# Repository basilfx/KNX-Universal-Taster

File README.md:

# KNX Universal Taster
DIY universal taster interface for the KNX bus.

## Introduction
This repository contains my designs for creating a custom KNX universal taster
interface (or actor). This is board that can be used for several purposes, but
its main purpose is to convert pulse-based wall switches into KNX-enabled
switches. The boards are designed to be small and should fit wall boxes with a
depth of 50 mm.

I currently have 25 boards installed in my house. As of writing (January 2021),
they have been running for more than two years.

## Features
While commercial alternatives exists, for example the [MDT Universal Interface](https://www.mdt.de/EN_Universal_Interface.html)
or the [ABB Universal Interface](https://new.abb.com/products/GHQ6310070R0111/us-u4-2-universal-interface-4-fold-fm),
I challenged myself to create a version that has more capabilities:

* Smaller.
* Programmable button options, e.g. multiple presses, long(er) presses.
* Support for (environmental) sensors.
* Universal use: data loggers, protocol gateways (Modbus, DSMR).
* Remote configuration via ETS or other software.

## Contents
You can find the following in this repository:

* [3D prints](3d) - Printable parts, such as an enclosure
* [Firmware](firmware) - Firmware files
* [PCB designs](pcb) - KiCad designs for the main PCB and extensions

## Support
You can buy the boards from [Aisler.net](https://aisler.net/p/GGKCSYBF), and
help me to support the development.

## License
The work in this repository is covered by CC BY-NC-SA 4.0. See the `LICENSE.md`
file for more information.

## Disclaimer
Use this project or information at your own risk. I cannot be held responsible
for any injuries or damages.

This page and its content is not affiliated with the KNX Association. Most
certainly, this work is not certified by the KNX Association.

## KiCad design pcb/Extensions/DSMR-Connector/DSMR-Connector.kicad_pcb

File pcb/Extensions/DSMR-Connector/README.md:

# DSMR-Connector

## Introduction
This board converts the P1 port found on Dutch Smart Energy Meters to UART,
opto-isolated from the Taster module. You can find more information in the
[P1 Companion Standard](https://www.netbeheernederland.nl/_upload/Files/Slimme_meter_15_a727fce1f1.pdf).

This board is only compatible with DSMR 5.0, since that version is using two
additional pins (therefore RJ-12 instead of RJ-11) to supply the bidirectional
optocoupler.

## Board

## Schema
You can find the schema [here](DSMR-Connector.pdf).

## BoM
The (interactive) BoM can be found [here](https://basilfx.github.io/KNX-Universal-Taster/pcb/Extensions/DSMR-Connector/BoM/ibom.html).

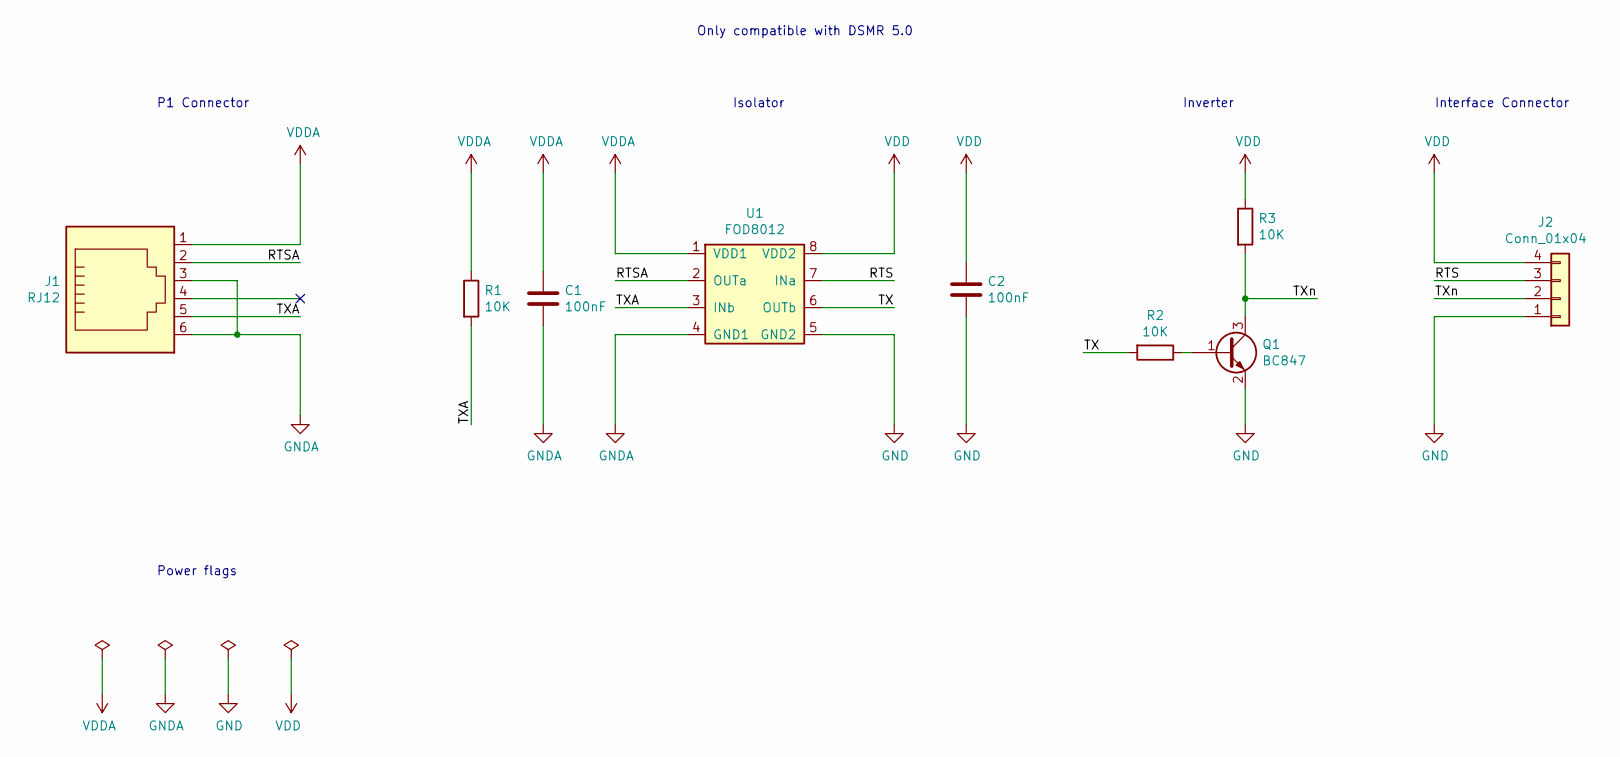
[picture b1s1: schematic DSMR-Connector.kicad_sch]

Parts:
C1, C2: 100nF; C_0603_1608Metric
J1: RJ12; RJ12_Amphenol_54601
J2: Conn_01x04; PinHeader_1x04_P1.27mm_Vertical
Q1: BC847; SOT-23
R1, R2, R3: 10K; R_0603_1608Metric
U1: FOD8012; SOIC-8-N

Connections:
/RTS: J2.3, U1.7 (INa)
/RTSA: J1.2, U1.2 (OUTa)
/TX: R2.2, U1.6 (OUTb)
/TXA: J1.5, R1.2, U1.3 (INb)
/TXn: J2.2, Q1.3 (C), R3.2
GND: C2.2, J2.1, Q1.2 (E), U1.5 (GND2)
GNDA: C1.2, J1.3, J1.6, U1.4 (GND1)
unnamed: Q1.1 (B), R2.1
VDD: C2.1, J2.4, R3.1, U1.8 (VDD2)
VDDA: C1.1, J1.1, R1.1, U1.1 (VDD1)

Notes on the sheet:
Inverter
Isolator
Power flags
P1 Connector
Only compatible with DSMR 5.0
Interface Connector

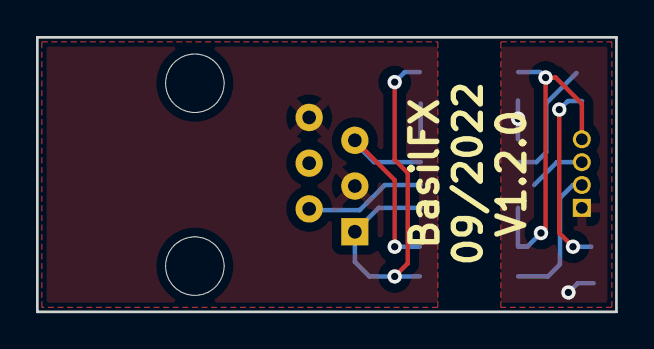
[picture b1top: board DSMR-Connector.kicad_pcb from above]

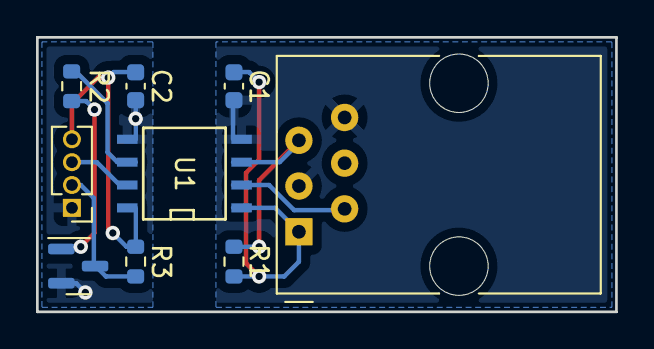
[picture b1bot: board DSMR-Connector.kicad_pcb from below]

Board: 2 copper layers, 32.2 x 15.2 mm, 9 parts (9 on the bottom side), 10 nets.

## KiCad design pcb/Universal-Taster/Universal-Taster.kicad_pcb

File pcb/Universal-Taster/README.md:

# Universal Taster

## Features
* ARM Cortex M4 CPU with 1 MiB of flash and 256 KiB of RAM
* Compatible with OnSemi NCN5120 and NCN5121
* 8 Mbit SPI NOR flash
* 6 universal GPIO pins
* 2 pins for I2C
* 2 RX/TX pins (without header)
* 30x30x15 mm footprint (including connector)

## Pictures

## Board

## Schema
You can find the schema [here](Universal-Taster.pdf).

## Compatibility
This board is compatible with the [OnSemi NCN5121](http://www.onsemi.com/pub/Collateral/NCN5121-D.PDF)
or the [OnSemi NCN5120](http://www.onsemi.com/pub/Collateral/NCN5120-D.PDF).

## BoM
The (interactive) BoM can be found [here](https://basilfx.github.io/KNX-Universal-Taster/pcb/Universal-Taster/BoM/ibom.html).

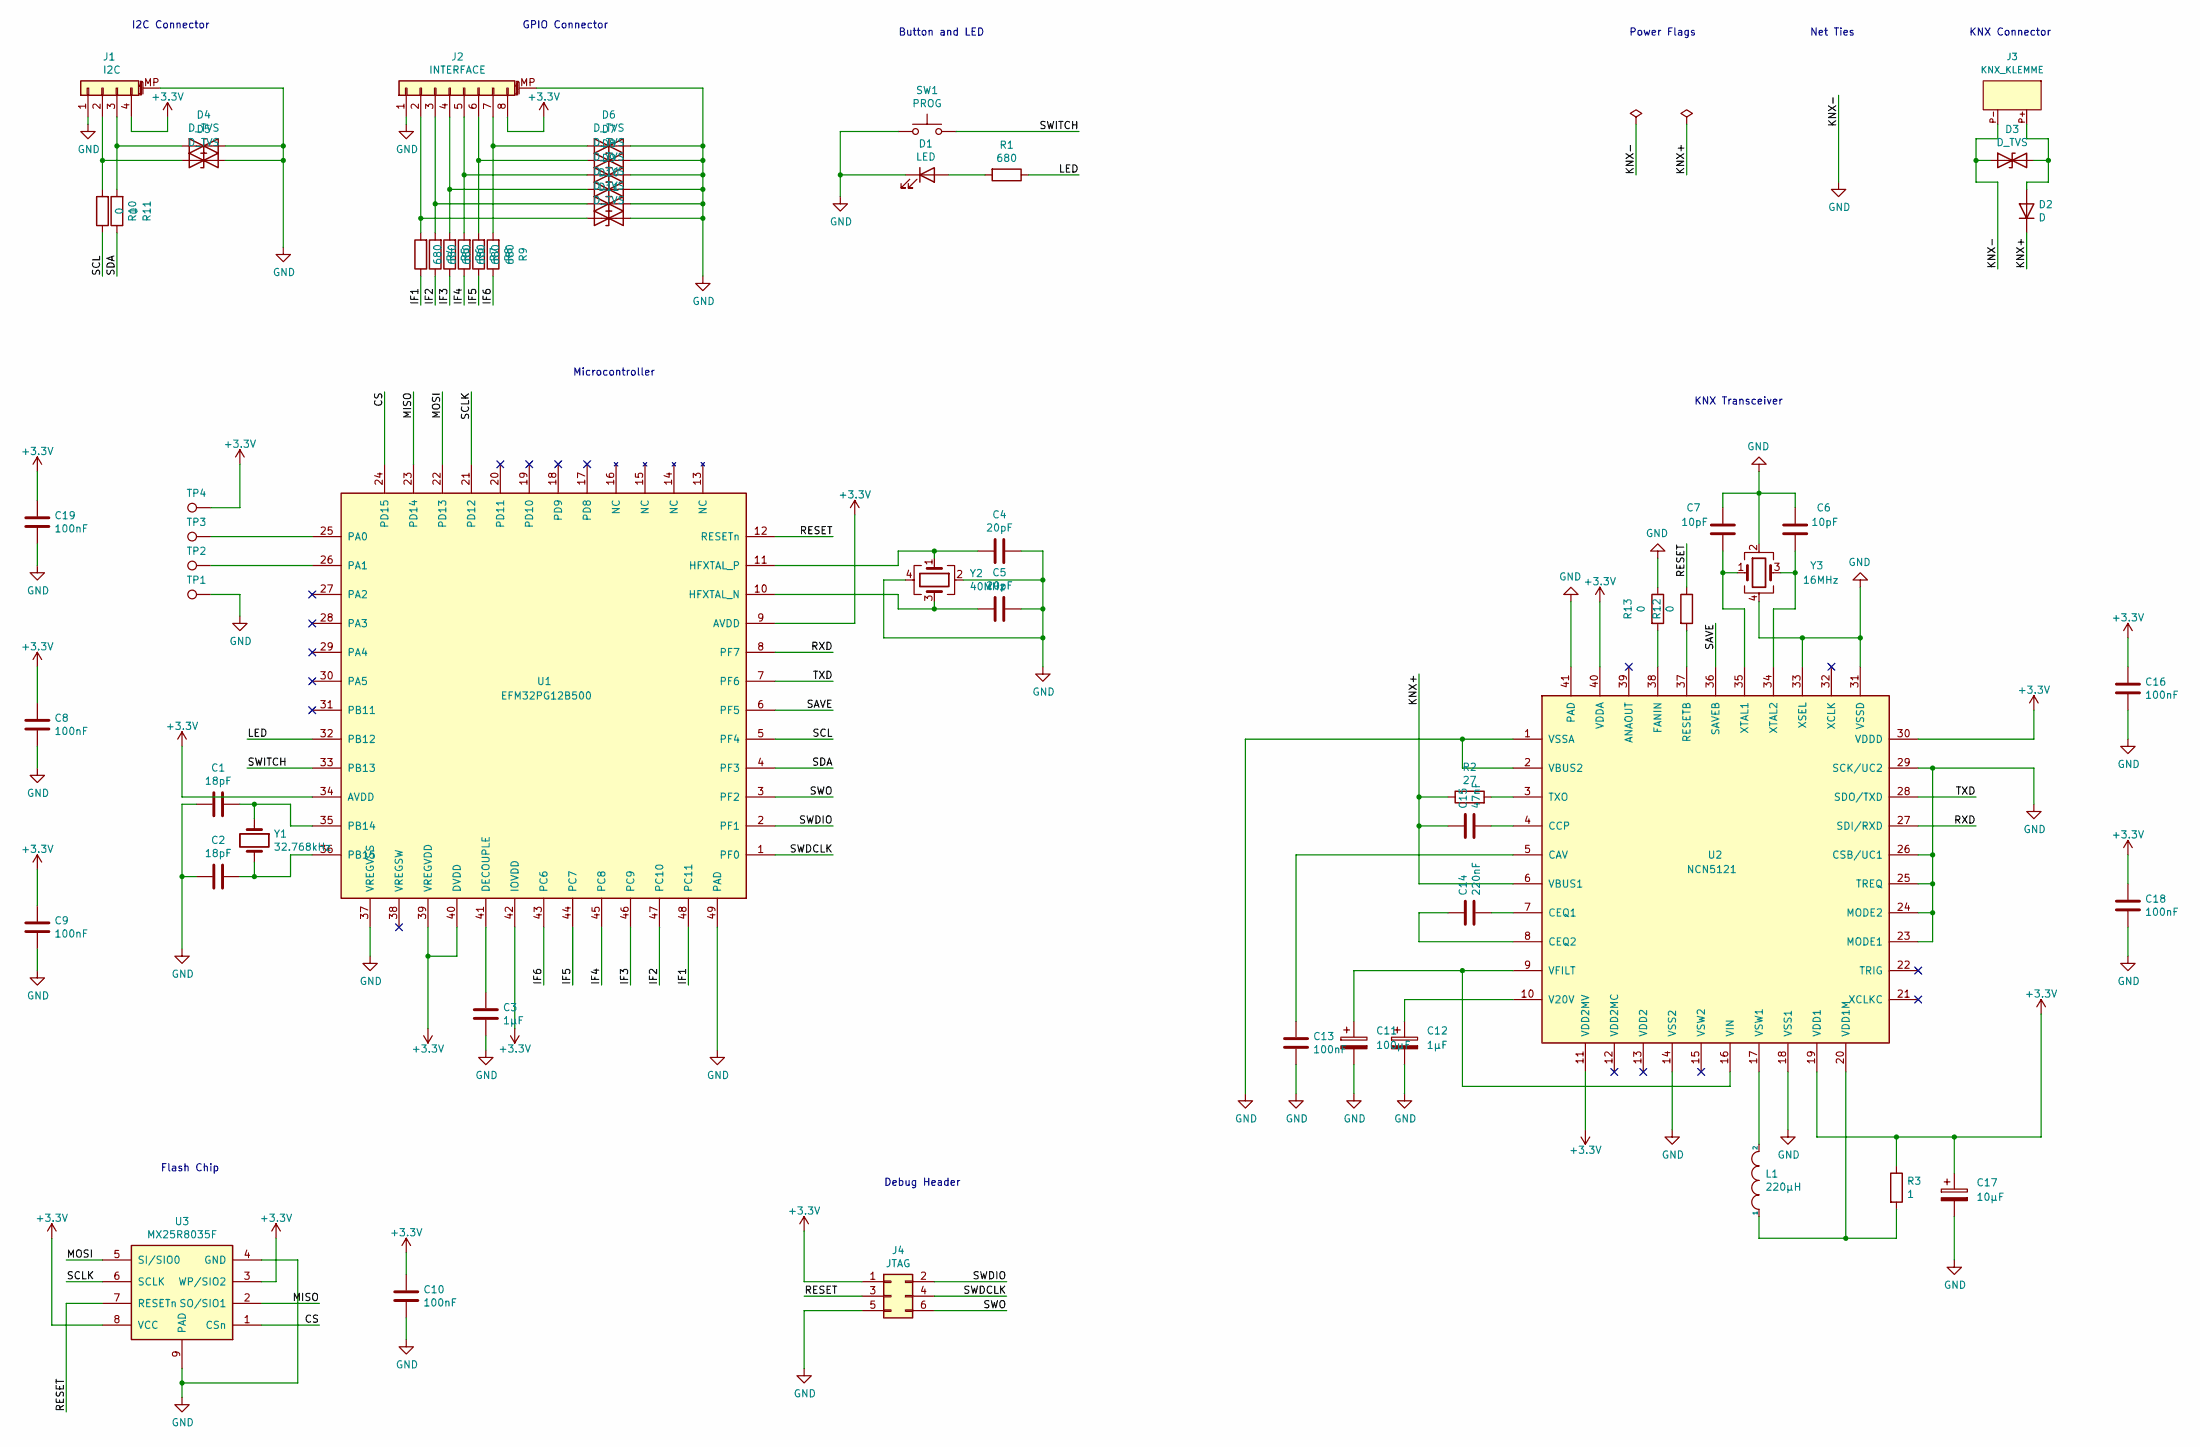
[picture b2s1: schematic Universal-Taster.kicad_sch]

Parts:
C1, C2: 18pF; C_0603_1608Metric
C3: 1µF; C_0603_1608Metric
C4, C5: 20pF; C_0603_1608Metric
C6, C7: 10pF; C_0603_1608Metric
C8, C9, C10, C13, C16, C18, C19: 100nF; C_0603_1608Metric
C11: 100µF; CP_Elec_6.3x7.7
C12: 1µF; C_0805_2012Metric
C14: 220nF; C_0603_1608Metric
C15: 47nF; C_0603_1608Metric
C17: 10µF; C_0603_1608Metric
D1: LED; LED_0603_1608Metric
D2: D; D_SMB
D3: D_TVS; D_SMB
D4, D5, D6, D7, D8, D9, D10, D11: D_TVS; D_0603_1608Metric
J1: I2C; JST_SH_BM04B-SRSS-TB_1x04-1MP_P1.00mm_Vertical
J2: INTERFACE; JST_SH_BM08B-SRSS-TB_1x08-1MP_P1.00mm_Vertical
J3: KNX_KLEMME
J4: JTAG; PinHeader_2x03_P1.27mm_Vertical_SMD
L1: 220µH; L_Bourns-SRR5028
R1, R4, R5, R6, R7, R8, R9: 680; R_0603_1608Metric
R2: 27; R_2512_6332Metric
R3: 1; R_0603_1608Metric
R10, R11, R12, R13: 0; R_0603_1608Metric
SW1: PROG; SW_SPST_B3U-1000P
TP1, TP2, TP3, TP4: Test_Point; TestPoint_Pad_D1.0mm
U1: EFM32PG12B500; Infineon_MLPQ-48-1EP_7x7mm_P0.5mm_Pad5.15x5.15mm
U2: NCN5121; QFN-40-1EP_6x6mm_P0.5mm_EP4.6x4.6mm
U3: MX25R8035F; USON-8_2x3mm_P0.5mm
Y1: 32.768kHz; Crystal_SMD_2012-2Pin_2.0x1.2mm
Y2: 40MHz; Crystal_SMD_2016-4Pin_2.0x1.6mm
Y3: 16MHz; Crystal_SMD_2016-4Pin_2.0x1.6mm

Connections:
+3.3V: C8.1, C9.1, C10.1, C16.1, C17.1, C18.1, C19.1, J1.4, J2.8, J4.1, R3.1, TP4.1, U1.9 (AVDD), U1.34 (AVDD), U1.39 (VREGVDD), U1.40 (DVDD), U1.42 (IOVDD), U2.11 (VDD2MV), U2.19 (VDD1), U2.30 (VDDD), U2.40 (VDDA), U3.3 (WP/SIO2), U3.8 (VCC)
/CS: U1.24 (PD15), U3.1 (CSn)
/IF1: R4.1, U1.48 (PC11)
/IF2: R5.1, U1.47 (PC10)
/IF3: R6.1, U1.46 (PC9)
/IF4: R7.1, U1.45 (PC8)
/IF5: R8.1, U1.44 (PC7)
/IF6: R9.1, U1.43 (PC6)
/KNX+: C15.1, D2.1 (K), R2.1, U2.6 (VBUS1)
/LED: R1.1, U1.32 (PB12)
/MISO: U1.23 (PD14), U3.2 (SO/SIO1)
/MOSI: U1.22 (PD13), U3.5 (SI/SIO0)
/RESET: J4.3, R12.1, U1.12 (RESETn), U3.7 (RESETn)
/RXD: U1.8 (PF7), U2.27 (SDI/RXD)
/SAVE: U1.6 (PF5), U2.36 (SAVEB)
/SCL: R10.1, U1.5 (PF4)
/SCLK: U1.21 (PD12), U3.6 (SCLK)
/SDA: R11.1, U1.4 (PF3)
/SWDCLK: J4.4, U1.1 (PF0)
/SWDIO: J4.2, U1.2 (PF1)
/SWITCH: SW1.2, U1.33 (PB13)
/SWO: J4.6, U1.3 (PF2)
/TXD: U1.7 (PF6), U2.28 (SDO/TXD)
GND: C1.1, C2.1, C3.2, C4.2, C5.2, C6.2, C7.2, C8.2, C9.2, C10.2, C11.2, C12.2, C13.2, C16.2, C17.2, C18.2, C19.2, D1.1 (K), D3.1 (A1), D4.2 (A2), D5.2 (A2), D6.2 (A2), D7.2 (A2), D8.2 (A2), D9.2 (A2), D10.2 (A2), D11.2 (A2), J1.1, J1.MP (MountPin), J2.1, J2.MP (MountPin), J3.P- (-), J4.5, R13.1, SW1.1, TP1.1, U1.37 (VREGVSS), U1.49 (PAD), U2.1 (VSSA), U2.2 (VBUS2), U2.14 (VSS2), U2.18 (VSS1), U2.23 (MODE1), U2.24 (MODE2), U2.25 (TREQ), U2.26 (CSB/UC1), U2.29 (SCK/UC2), U2.31 (VSSD), U2.33 (XSEL), U2.41 (PAD), U3.4 (GND), U3.9 (PAD), Y2.2, Y2.4, Y3.2, Y3.4
unnamed: C1.2, U1.35 (PB14), Y1.1
unnamed: C2.2, U1.36 (PB15), Y1.2
unnamed: C3.1, U1.41 (DECOUPLE)
unnamed: C4.1, U1.11 (HFXTAL_P), Y2.1
unnamed: C5.1, U1.10 (HFXTAL_N), Y2.3
unnamed: C6.1, U2.34 (XTAL2), Y3.3
unnamed: C7.1, U2.35 (XTAL1), Y3.1
unnamed: C11.1, U2.9 (VFILT), U2.16 (VIN)
unnamed: C12.1, U2.10 (V20V)
unnamed: C13.1, U2.5 (CAV)
unnamed: C14.1, U2.8 (CEQ2)
unnamed: C14.2, U2.7 (CEQ1)
unnamed: C15.2, U2.4 (CCP)
unnamed: D1.2 (A), R1.2
unnamed: D2.2 (A), D3.2 (A2), J3.P+ (+)
unnamed: D4.1 (A1), J1.3, R11.2
unnamed: D5.1 (A1), J1.2, R10.2
unnamed: D6.1 (A1), J2.7, R9.2
unnamed: D7.1 (A1), J2.6, R8.2
unnamed: D8.1 (A1), J2.5, R7.2
unnamed: D9.1 (A1), J2.4, R6.2
unnamed: D10.1 (A1), J2.3, R5.2
unnamed: D11.1 (A1), J2.2, R4.2
unnamed: L1.1, R3.2, U2.20 (VDD1M)
unnamed: L1.2, U2.17 (VSW1)
unnamed: R2.2, U2.3 (TXO)
unnamed: R12.2, U2.37 (RESETB)
unnamed: R13.2, U2.38 (FANIN)
unnamed: TP2.1, U1.26 (PA1)
unnamed: TP3.1, U1.25 (PA0)

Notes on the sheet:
Power Flags
KNX Transceiver
I2C Connector
Debug Header
Net Ties
GPIO Connector
Microcontroller
Button and LED
KNX Connector
Flash Chip

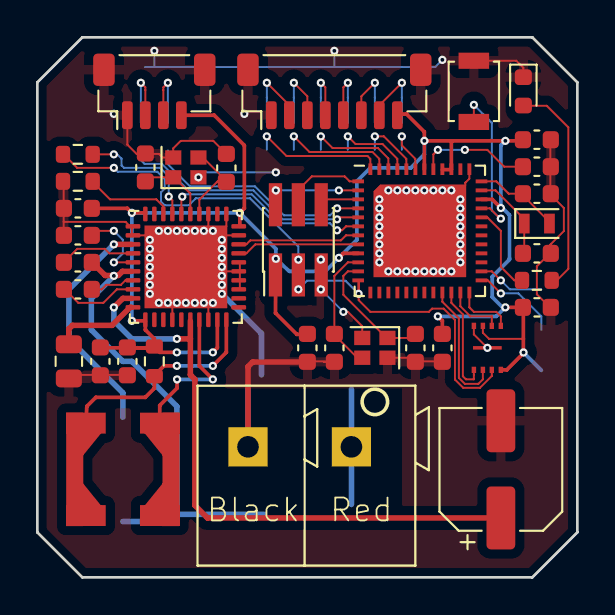
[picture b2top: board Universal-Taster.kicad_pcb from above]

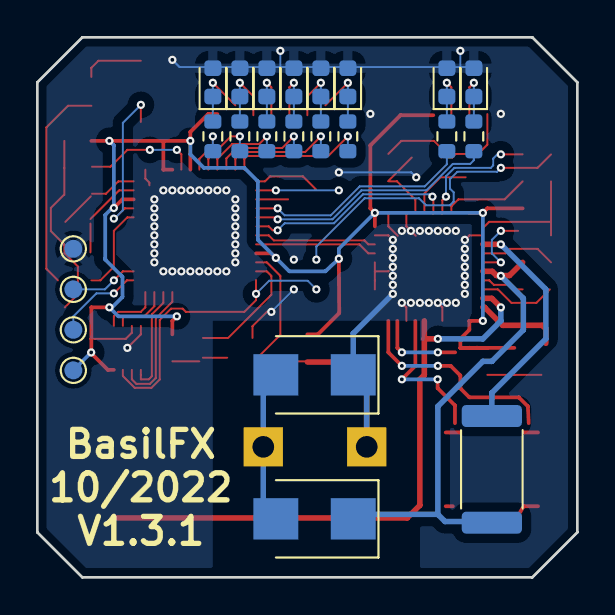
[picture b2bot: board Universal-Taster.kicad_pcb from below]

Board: 2 copper layers, 30.0 x 30.0 mm, 59 parts (23 on the bottom side), 54 nets.

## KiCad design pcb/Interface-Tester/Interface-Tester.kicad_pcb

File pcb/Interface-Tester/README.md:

# Interface Tester

## Introduction
This is an interface tester for the taster board. It is used for verification
purposes

## Board

## Schema
You can find the schema [here](Interface-Tester.pdf).

## BoM
The (interactive) BoM can be found [here](https://basilfx.github.io/KNX-Universal-Taster/pcb/Interface-Tester/BoM/ibom.html).

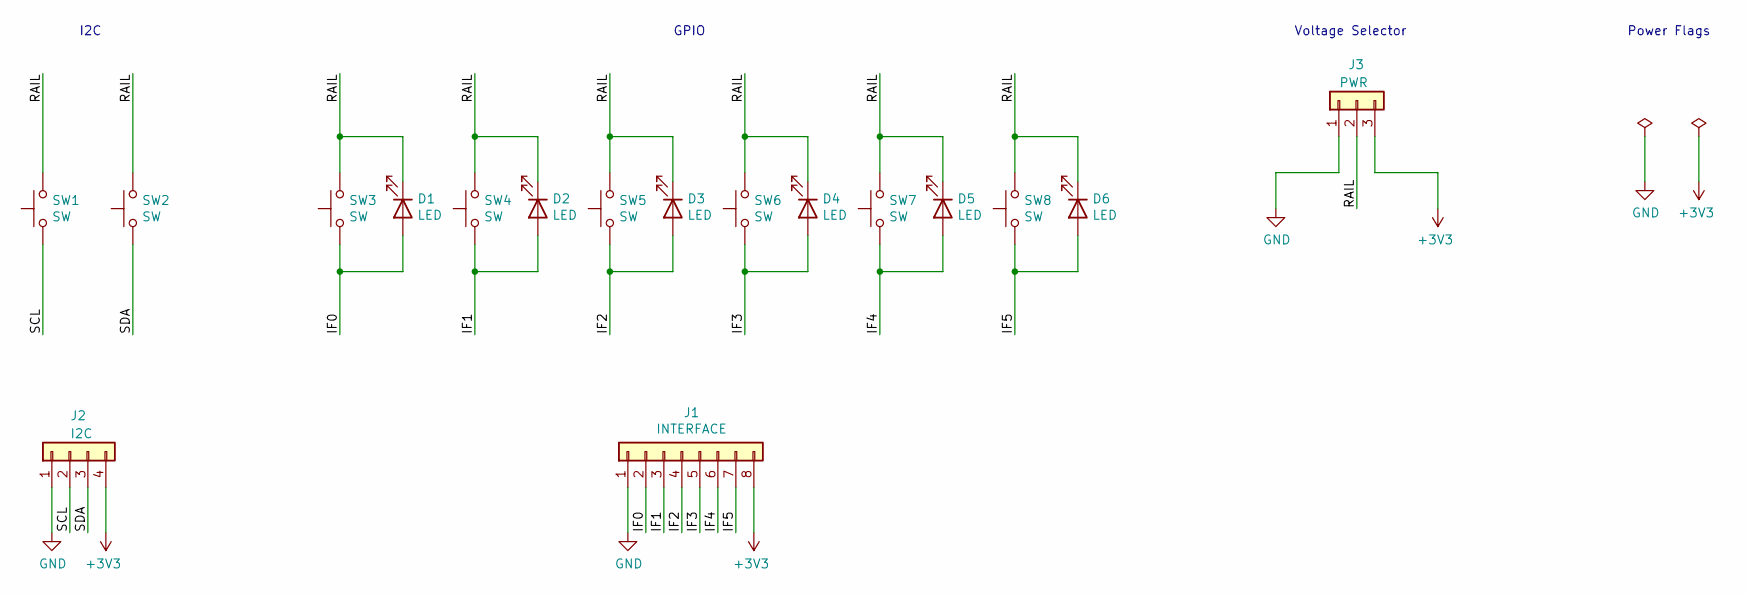
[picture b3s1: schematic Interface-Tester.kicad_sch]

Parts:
D1, D2, D3, D4, D5, D6: LED; LED_0603_1608Metric
J1: INTERFACE; PinHeader_1x08_P2.54mm_Vertical
J2: I2C; PinHeader_1x04_P2.54mm_Vertical
J3: PWR; PinHeader_1x03_P2.54mm_Vertical
SW1, SW2, SW3, SW4, SW5, SW6, SW7, SW8: SW; SW_PUSH_6mm

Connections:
+3V3: J1.8, J2.4, J3.3
/IF0: D1.2 (A), J1.2, SW3.1
/IF1: D2.2 (A), J1.3, SW4.1
/IF2: D3.2 (A), J1.4, SW5.1
/IF3: D4.2 (A), J1.5, SW6.1
/IF4: D5.2 (A), J1.6, SW7.1
/IF5: D6.2 (A), J1.7, SW8.1
/RAIL: D1.1 (K), D2.1 (K), D3.1 (K), D4.1 (K), D5.1 (K), D6.1 (K), J3.2, SW1.2, SW2.2, SW3.2, SW4.2, SW5.2, SW6.2, SW7.2, SW8.2
/SCL: J2.2, SW1.1
/SDA: J2.3, SW2.1
GND: J1.1, J2.1, J3.1

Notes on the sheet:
Voltage Selector
GPIO
Power Flags
I2C

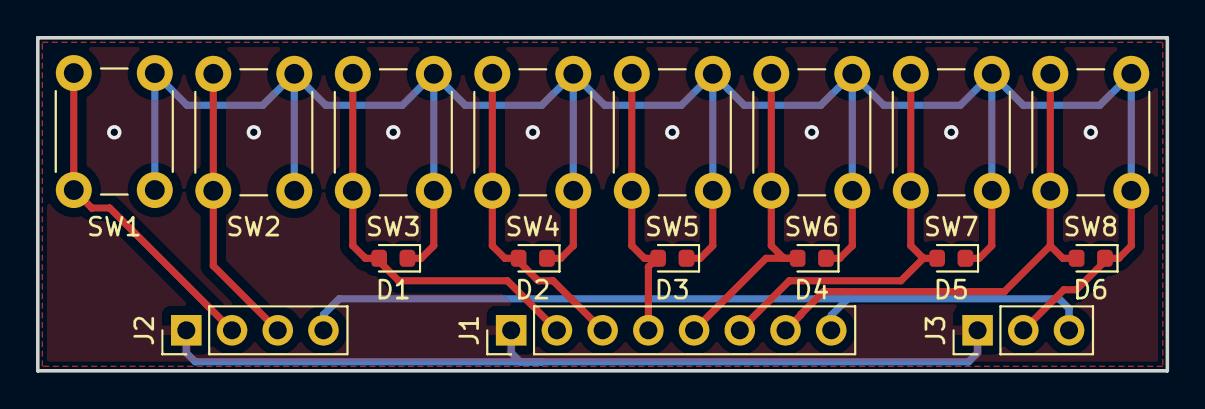
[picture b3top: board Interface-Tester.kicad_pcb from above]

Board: 2 copper layers, 62.8 x 18.5 mm, 17 parts (0 on the bottom side), 11 nets.

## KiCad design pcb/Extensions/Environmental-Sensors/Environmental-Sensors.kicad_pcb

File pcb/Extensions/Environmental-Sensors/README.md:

# Environmental-Sensors

## Board

## Schema
You can find the schema [here](Environmental-Sensors.pdf).

## BoM
The (interactive) BoM can be found [here](https://basilfx.github.io/KNX-Universal-Taster/pcb/Extensions/Environmental-Sensors/BoM/ibom.html).

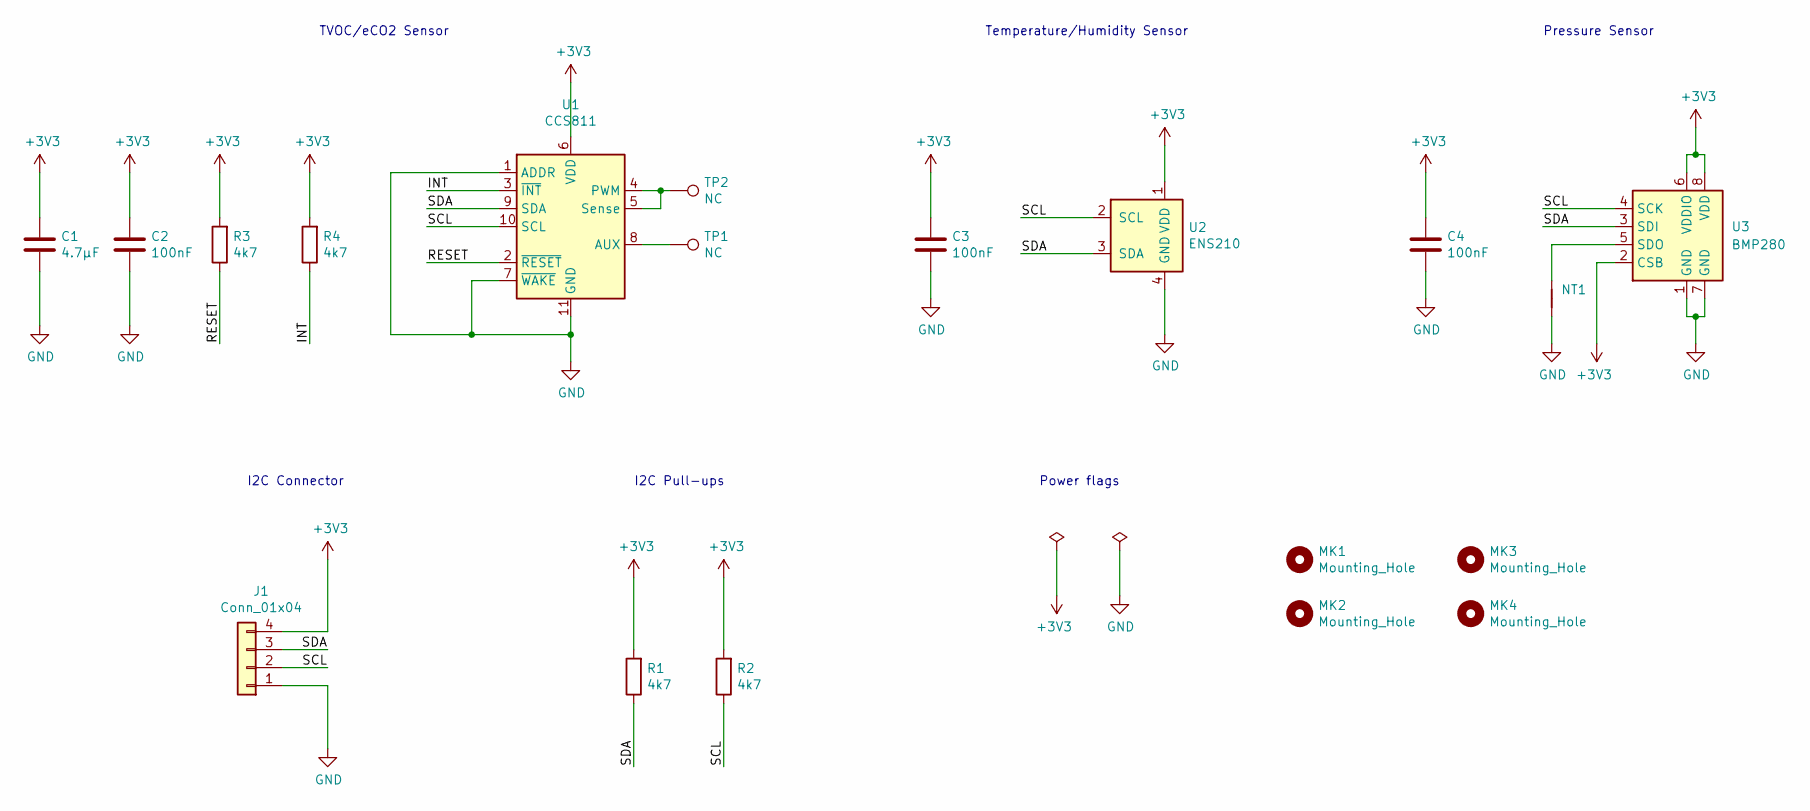
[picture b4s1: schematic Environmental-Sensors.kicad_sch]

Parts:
C1: 4.7µF; C_0402_1005Metric
C2, C3, C4: 100nF; C_0402_1005Metric
J1: Conn_01x04; PinHeader_1x04_P1.27mm_Vertical
MK1, MK2, MK3, MK4: Mounting_Hole; TestPoint_Plated_Hole_D2.0mm
NT1: NetTie_2; NetTie-2_SMD_Pad0.25mm
R1, R2, R3, R4: 4k7; R_0402_1005Metric
TP1, TP2: NC; TestPoint_Pad_D1.0mm
U1: CCS811; AMS_LGA-10-1EP_2.7x4mm_P0.6mm
U2: ENS210; AMS_QFN-4-1EP_2x2mm_P0.95mm_EP0.7x1.6mm
U3: BMP280; Bosch_LGA-8_2x2.5mm_P0.65mm_ClockwisePinNumbering; MPN BMP280

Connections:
+3V3: C1.1, C2.1, C3.1, C4.1, J1.4, R1.2, R2.2, R3.2, R4.2, U1.6 (VDD), U2.1 (VDD), U3.2 (CSB), U3.6 (VDDIO), U3.8 (VDD)
/INT: R4.1, U1.3 (~INT)
/RESET: R3.1, U1.2 (~RESET)
/SCL: J1.2, R2.1, U1.10 (SCL), U2.2 (SCL), U3.4 (SCK)
/SDA: J1.3, R1.1, U1.9 (SDA), U2.3 (SDA), U3.3 (SDI)
GND: C1.2, C2.2, C3.2, C4.2, J1.1, NT1.1, U1.1 (ADDR), U1.7 (~WAKE), U1.11 (GND), U2.4 (GND), U2.5 (GND), U3.1 (GND), U3.7 (GND)
unnamed: NT1.2, U3.5 (SDO)
unnamed: TP1.1, U1.8 (AUX)
unnamed: TP2.1, U1.4 (PWM), U1.5 (Sense)

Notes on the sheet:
TVOC/eCO2 Sensor
Power flags
Temperature/Humidity Sensor
I2C Connector
Pressure Sensor
I2C Pull-ups

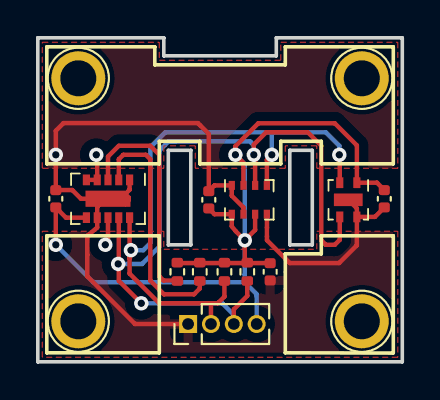
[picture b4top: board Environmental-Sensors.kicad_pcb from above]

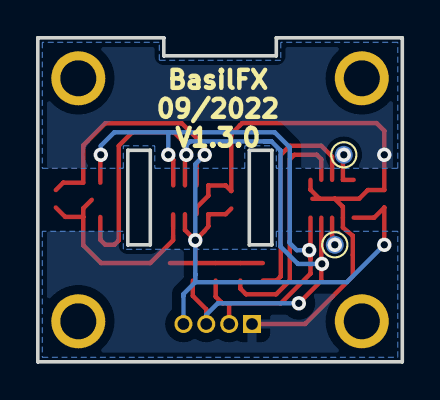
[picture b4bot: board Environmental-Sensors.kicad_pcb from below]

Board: 2 copper layers, 20.2 x 18.0 mm, 19 parts (2 on the bottom side), 9 nets.

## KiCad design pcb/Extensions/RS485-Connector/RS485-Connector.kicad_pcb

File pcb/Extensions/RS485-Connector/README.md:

# RS485-Connector

## Introduction
Isolated RS485 converter, full and half duplex.

## Board

## Schema
You can find the schema [here](RS485-Connector.pdf).

## BoM
The (interactive) BoM can be found [here](https://basilfx.gthub.io/KNX-Universal-Taster/pcb/Extensions/RS485-Connector/BoM/ibom.html).

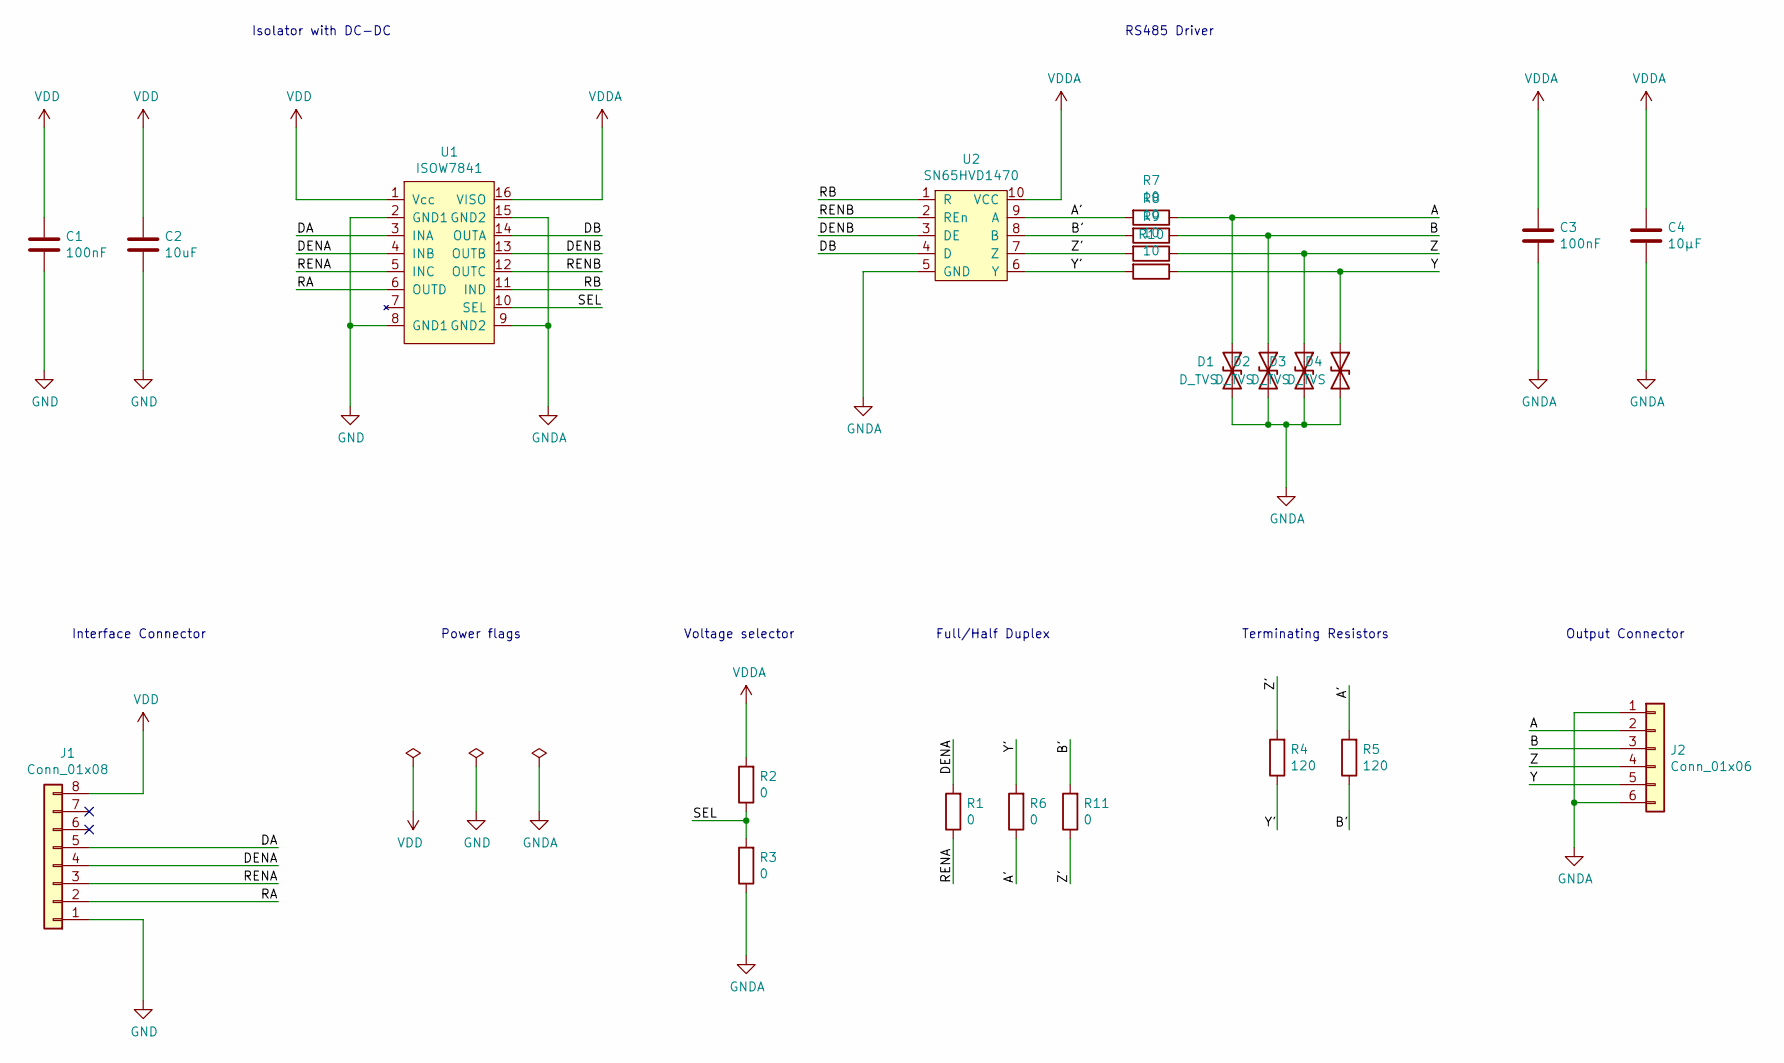
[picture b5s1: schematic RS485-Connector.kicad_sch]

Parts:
C1, C3: 100nF; C_0603_1608Metric
C2: 10uF; C_0603_1608Metric
C4: 10µF; C_0603_1608Metric
D1, D2, D3, D4: D_TVS; D_0603_1608Metric
J1: Conn_01x08; PinHeader_1x08_P1.27mm_Vertical
J2: Conn_01x06; TerminalBlock_TE_282834-6_1x06_P2.54mm_Horizontal
R1, R2, R3, R6, R11: 0; R_0603_1608Metric
R4, R5: 120; R_0603_1608Metric
R7, R8, R9, R10: 10; R_0603_1608Metric
U1: ISOW7841; SOIC-16W_7.5x10.3mm_P1.27mm
U2: SN65HVD1470; MSOP-10_3x3mm_P0.5mm

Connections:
/A: D1.1 (A1), J2.2, R7.1
/A': R5.2, R6.1, R7.2, U2.9 (A)
/B: D2.1 (A1), J2.3, R8.1
/B': R5.1, R8.2, R11.2, U2.8 (B)
/DA: J1.5, U1.3 (INA)
/DB: U1.14 (OUTA), U2.4 (D)
/DENA: J1.4, R1.2, U1.4 (INB)
/DENB: U1.13 (OUTB), U2.3 (DE)
/RA: J1.2, U1.6 (OUTD)
/RB: U1.11 (IND), U2.1 (R)
/RENA: J1.3, R1.1, U1.5 (INC)
/RENB: U1.12 (OUTC), U2.2 (REn)
/SEL: R2.1, R3.2, U1.10 (SEL)
/Y: D4.1 (A1), J2.5, R10.1
/Y': R4.1, R6.2, R10.2, U2.6 (Y)
/Z: D3.1 (A1), J2.4, R9.1
/Z': R4.2, R9.2, R11.1, U2.7 (Z)
GND: C1.2, C2.2, J1.1, U1.2 (GND1), U1.8 (GND1)
GNDA: C3.2, C4.2, D1.2 (A2), D2.2 (A2), D3.2 (A2), D4.2 (A2), J2.1, J2.6, R3.1, U1.9 (GND2), U1.15 (GND2), U2.5 (GND)
VDD: C1.1, C2.1, J1.8, U1.1 (Vcc)
VDDA: C3.1, C4.1, R2.2, U1.16 (VISO), U2.10 (VCC)

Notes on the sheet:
Terminating Resistors
RS485 Driver
Interface Connector
Power flags
Output Connector
Voltage selector
Isolator with DC-DC
Full/Half Duplex

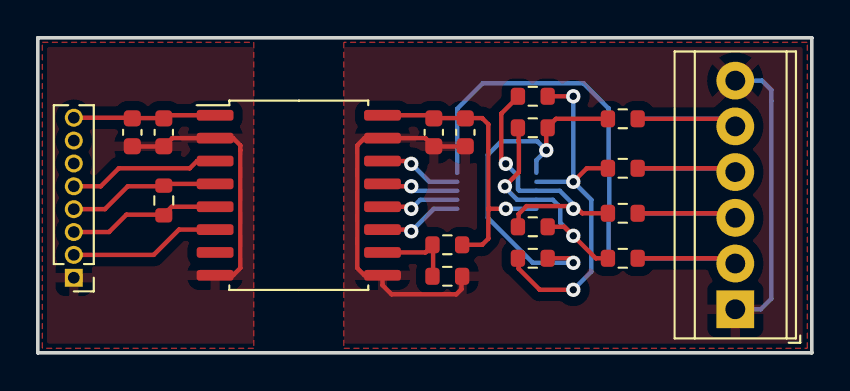
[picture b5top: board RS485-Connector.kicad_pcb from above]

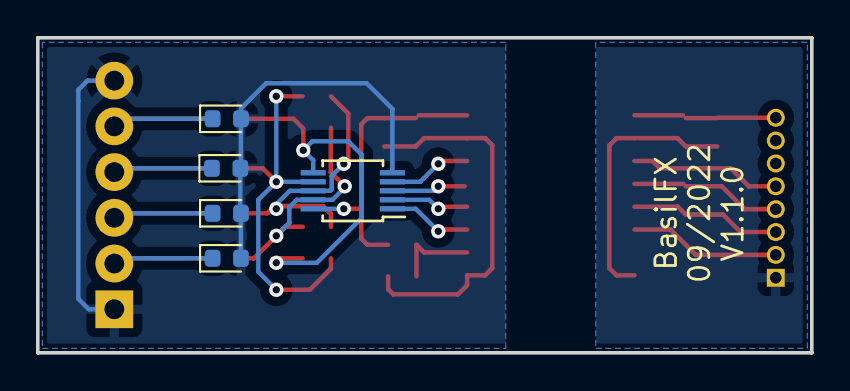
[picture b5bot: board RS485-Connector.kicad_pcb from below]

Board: 2 copper layers, 43.0 x 17.5 mm, 23 parts (5 on the bottom side), 21 nets.

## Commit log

2018-06-11 Add gitignore.
2018-08-13 Add README.md and LICENSE.md.
2018-08-13 Add taster
2018-08-13 Version 1.1.0 of the Taster board.
2018-08-13 Prepare repository for publishing.
2018-08-13 Add sensors.
2018-08-13 Add interface tester.
2018-08-20 Version 1.2.0 of board
2018-08-20 Version 1.1.0 of interface tester.
2018-08-21 Move and rename Sensors to Environmental-Sensors.
2018-08-21 Added board v1.1.0 of environmental sensors
2018-08-22 Added version 1.2.0 of environmental sensors board.
2018-08-26 Add DSMR Connector v1.0.0
2018-08-26 Add RS-485 module version 1.0.0
2021-01-25 Restructure repository.
2021-01-25 Add images of soldered boards.
2021-01-25 Add enclosure.
2021-01-25 Add firmware files.
2021-07-15 Correct symbol library table paths.
2021-07-15 Version 1.2.1 of Universal-Taster
    - More clearance of traces around resistor SCL line
    - Fixed DRC errors (new in Kicad 5.1.x)
2021-07-15 Updated gitignore.
2021-07-15 Updated DSMR-Connector after first tests.
2021-07-15 DSMR-Connector v1.1.0
    - Add missing pull-up resistor
    - Add signal inverter.
2022-09-14 Fix (and convert) hardcoded path to 3D model
2022-09-14 Ignore backup folder.
2022-09-27 Upgrade Universal Taster to KiCad 6.0
2022-09-27 Upgrade Interface Tester to KiCad 6.0
2022-09-27 Upgrade RS485 Connector to KiCad 6.0
2022-09-27 Upgrade Environmental Sensors to KiCad 6.0
2022-09-27 Upgrade DSMR Connector to KiCad 6.0
2022-09-27 Properly rename Taster to Universal-Taster
2022-09-27 Correct typo
2022-09-27 Correct URLs of files and folders
2022-10-03 Fix universal taster
2022-10-03 Add GitHub action to publish interactive BoM
2022-10-03 Add interactive BoM to Universal Taster
2022-10-03 Add interactive BoM to Environmental Sensors
2022-10-03 Add interactive BoM to Interface Tester
2022-10-03 Add interactive BoM to RS485 Connector
2022-10-03 Add interactive BoM to DSMR Connector
2022-10-03 Add Tracespace board render settings
2022-10-03 Replace 3D pictures with 2D images for DSMR Connector
2022-10-03 Replace 3D pictures with 2D images for Environmental Sensors
2022-10-03 Replace 3D pictures with 2D images for RS485 Connector
2022-10-03 Replace 3D pictures with 2D pictures for Interface Tester
2022-10-03 Replace 3D pictures with 2D pictures for Universal Taster
2025-01-06 Add firmware v0.4.0
    The slot0.4.bin and slot1.4.bin are update files.
2025-01-06 Update documentation
